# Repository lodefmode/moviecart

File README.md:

# moviecart
Software and Hardware to create full length color movie + audio cartridges for stock Atari 2600

[How to watch different files:](docs/How_To_Update_Content.txt)

[How to encode your own:](https://www.youtube.com/watch?v=WSy6kNrYDSo&list=PLHJZWs7or3edcvVHDeNzGSZABx2JN1WZH)

Pre-Order Kits at:

https://www.tindie.com/products/lodefmode/moviecart-atari-2600/

September 11 1977
-

Introducing MovieCart.

This revolutionary new product will allow for the first time ever, anyone to experience the joy of the silver screen directly from the comfort of their own home, in stunning digital accuracy.
Boasting an impressive 80 x 192 resolution, 7 bit color and 4 bit monaural audio, begin building your full length feature film library today.*

Technical Specs:

   Two fields are alternated at 60 frames per second.
   Each field consists of a checkerboard pattern of 10 x 262 cells.
   Each cell contains one of 128 colours and is 8 pixels wide by 1 pixel deep.
   This produces an effective resolution of 80 x 262 @ 30 frames per second, with 10 colors per line.
   
   Sound is 4 bit mono produced at 15.720 KHz.

   Joystick controls brightness, volume, and shuttle position.
   Console switches control b/w, ten second rewind and full rewind.

   Each field requires 2.5K of data.
   Each second requires the equivalent of 75.5 Combat cartridges, or over half a million cartridges to produce a full length 2 hour movie.

Thanks,

lodef.mode@gmail.com

*Copyright Disclaimer under Section 107 of the copyright act 1976, allowance is made for fair use for purposes such as criticism, comment, news reporting, scholarship, and research. Fair use is a use permitted by copyright statute that might otherwise be infringing. Non-profit, educational or personal use tips the balance in favour of fair use."

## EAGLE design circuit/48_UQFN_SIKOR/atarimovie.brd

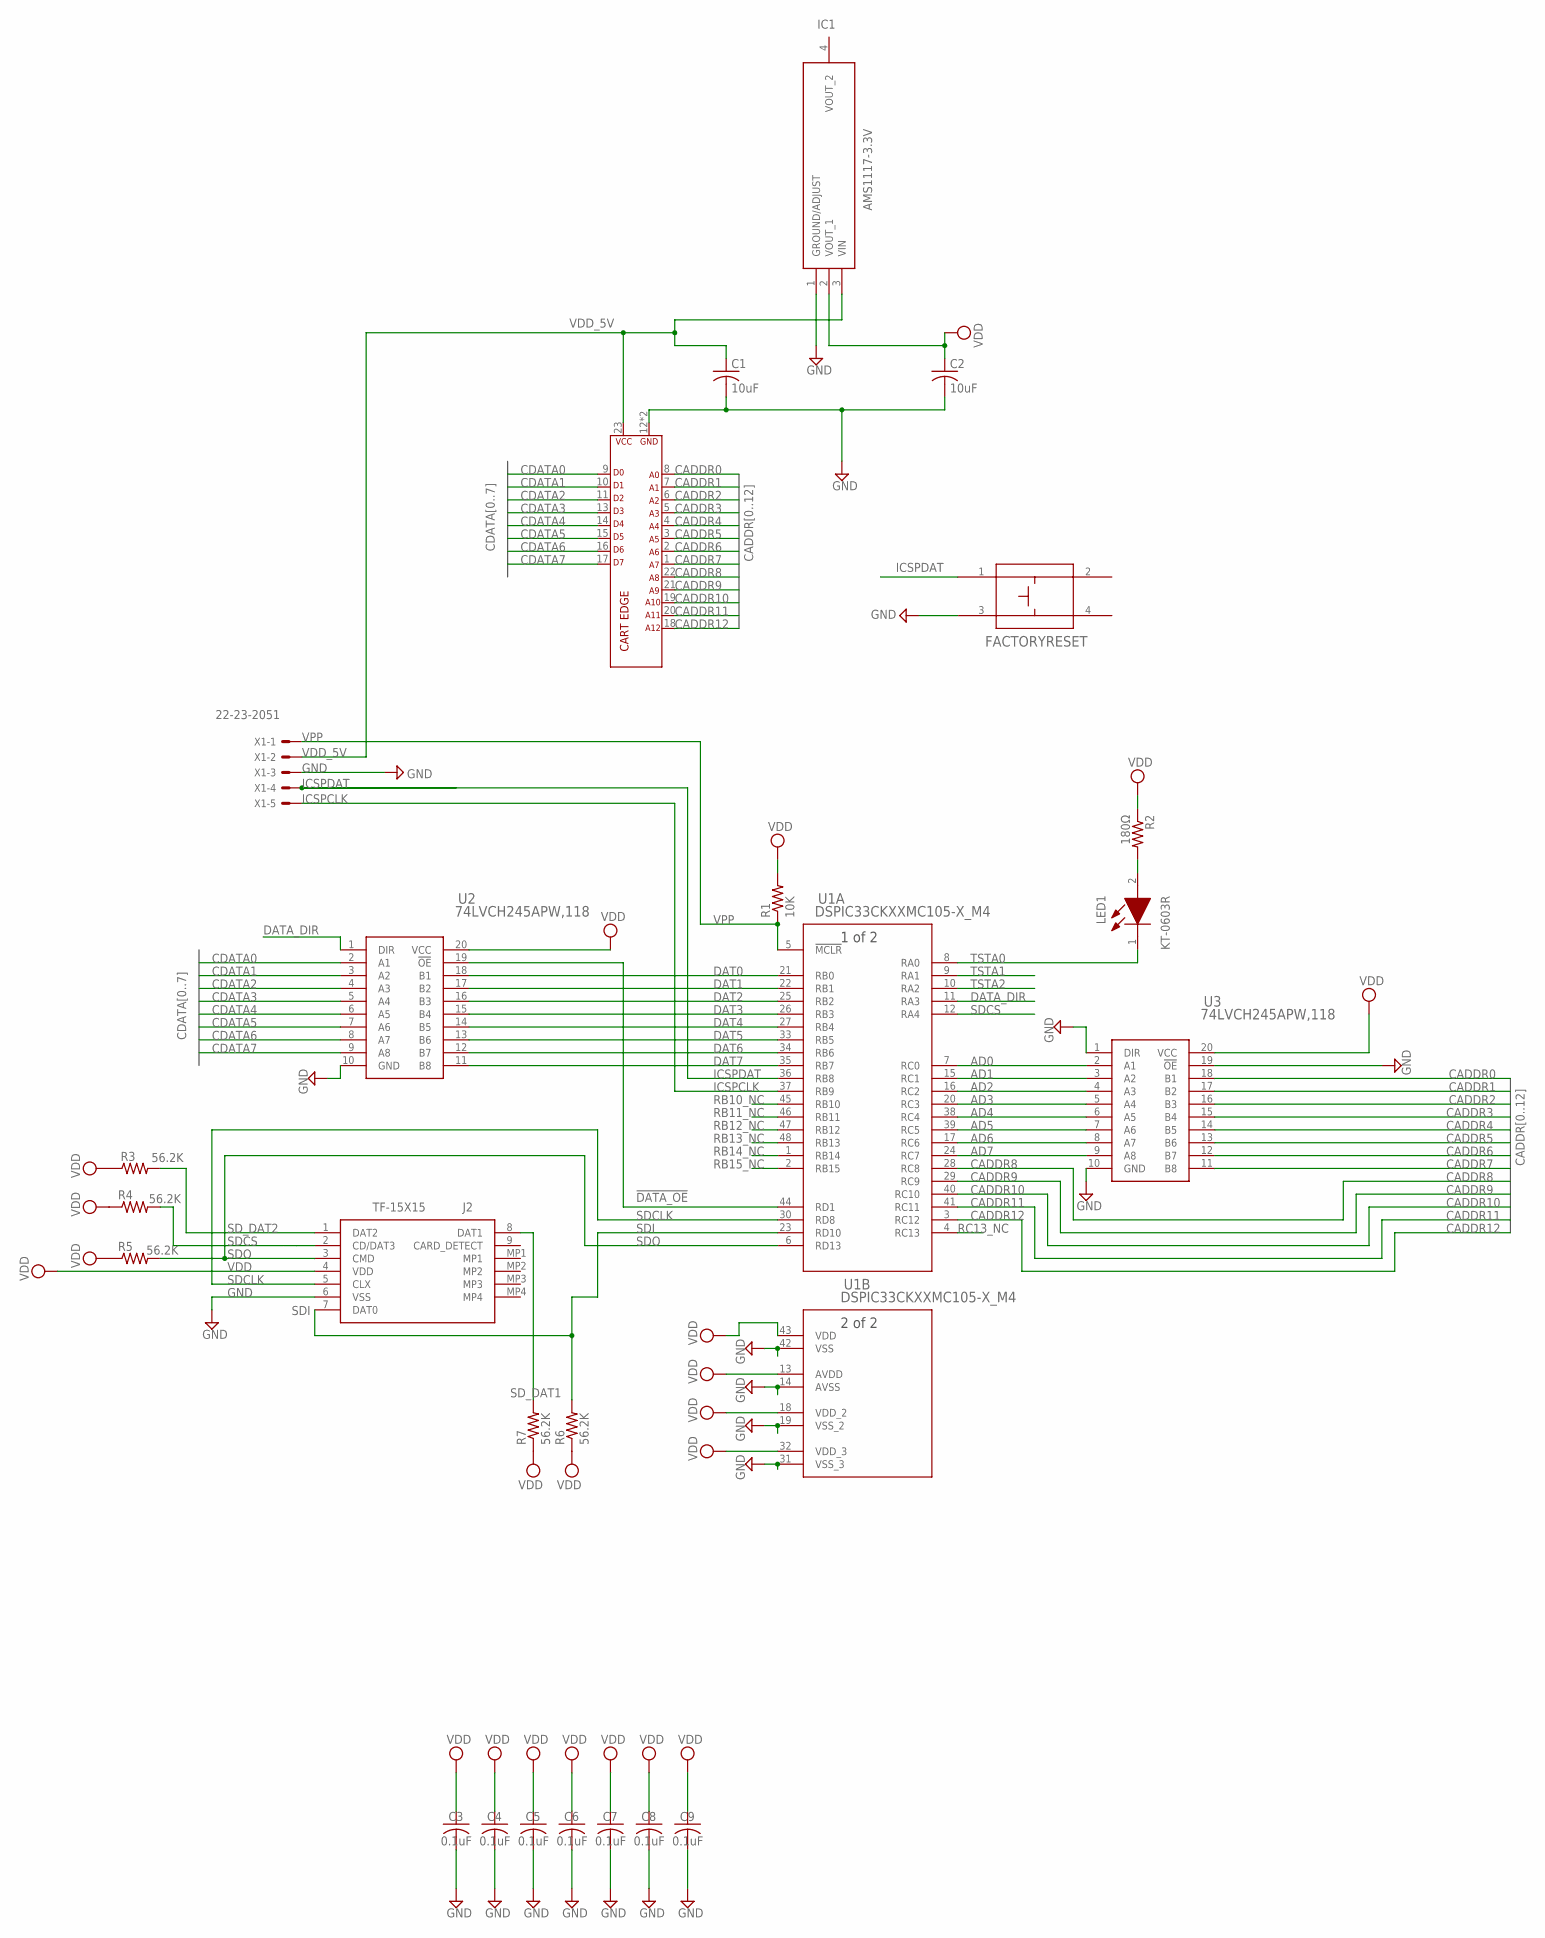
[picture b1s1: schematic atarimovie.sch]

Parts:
C1, C2: 10uF; C0603K
C3, C4, C5, C6, C7, C8, C9: 0.1uF; C0603K
FACTORYRESET: RT3301AF260Q; RT3301_EWI
IC1: AMS1117-3.3V; SOT229P700X180-4N
J1: CARTRIDGE EDGE; MED_TABS_SDACCESS
J2: TF-15X15; TF15X15
LED1: KT-0603R; LEDC1608X70N
R1: 10K; R0603
R2: 180Ω; R0603
R3, R4, R5, R6, R7: 56.2K; R0603
U1: DSPIC33CKXXMC105-X_M4; UQFN48_6X6MC_MCH
U2, U3: 74LVCH245APW,118; SOP65P640X110-20N
X1: 22-23-2051

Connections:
!DATA_OE!: U1.44 (RD1), U2.19 (!OE)
AD0: U1.7 (RC0), U3.2 (A1)
AD1: U1.15 (RC1), U3.3 (A2)
AD2: U1.16 (RC2), U3.4 (A3)
AD3: U1.20 (RC3), U3.5 (A4)
AD4: U1.38 (RC4), U3.6 (A5)
AD5: U1.39 (RC5), U3.7 (A6)
AD6: U1.17 (RC6), U3.8 (A7)
AD7: U1.24 (RC7), U3.9 (A8)
CADDR0: J1.8 (A0), U3.18 (B1)
CADDR1: J1.7 (A1), U3.17 (B2)
CADDR2: J1.6 (A2), U3.16 (B3)
CADDR3: J1.5 (A3), U3.15 (B4)
CADDR4: J1.4 (A4), U3.14 (B5)
CADDR5: J1.3 (A5), U3.13 (B6)
CADDR6: J1.2 (A6), U3.12 (B7)
CADDR7: J1.1 (A7), U3.11 (B8)
CADDR8: J1.22 (A8), U1.28 (RC8)
CADDR9: J1.21 (A9), U1.29 (RC9)
CADDR10: J1.19 (A10), U1.40 (RC10)
CADDR11: J1.20 (A11), U1.41 (RC11)
CADDR12: J1.18 (A12), U1.3 (RC12)
CDATA0: J1.9 (D0), U2.2 (A1)
CDATA1: J1.10 (D1), U2.3 (A2)
CDATA2: J1.11 (D2), U2.4 (A3)
CDATA3: J1.13 (D3), U2.5 (A4)
CDATA4: J1.14 (D4), U2.6 (A5)
CDATA5: J1.15 (D5), U2.7 (A6)
CDATA6: J1.16 (D6), U2.8 (A7)
CDATA7: J1.17 (D7), U2.9 (A8)
DAT0: U1.21 (RB0), U2.18 (B1)
DAT1: U1.22 (RB1), U2.17 (B2)
DAT2: U1.25 (RB2), U2.16 (B3)
DAT3: U1.26 (RB3), U2.15 (B4)
DAT4: U1.27 (RB4), U2.14 (B5)
DAT5: U1.33 (RB5), U2.13 (B6)
DAT6: U1.34 (RB6), U2.12 (B7)
DAT7: U1.35 (RB7), U2.11 (B8)
DATA_DIR: U1.11 (RA3), U2.1 (DIR)
GND: C1.2, C2.2, C3.2, C4.2, C5.2, C6.2, C7.2, C8.2, C9.2, FACTORYRESET.3, IC1.1 (GROUND/ADJUST), J1.12 (GND), J1.24 (GND), J2.6 (VSS), U1.14 (AVSS), U1.19 (VSS_2), U1.31 (VSS_3), U1.42 (VSS), U2.10 (GND), U3.1 (DIR), U3.10 (GND), U3.19 (!OE), X1.3
ICSPCLK: U1.37 (RB9), X1.5
ICSPDAT: FACTORYRESET.1, U1.36 (RB8), X1.4
unnamed: LED1.2 (A), R2.2
RB10_NC: U1.45 (RB10)
RB11_NC: U1.46 (RB11)
RB12_NC: U1.47 (RB12)
RB13_NC: U1.48 (RB13)
RB14_NC: U1.1 (RB14)
RB15_NC: U1.2 (RB15)
RC13_NC: U1.4 (RC13)
SDCLK: J2.5 (CLX), U1.30 (RD8)
SDCS: J2.2 (CD/DAT3), R4.2, U1.12 (RA4)
SDI: J2.7 (DAT0), R6.2, U1.23 (RD10)
SDO: J2.3 (CMD), R5.2, U1.6 (RD13)
SD_DAT1: J2.8 (DAT1), R7.2
SD_DAT2: J2.1 (DAT2), R3.2
TSTA0: LED1.1 (K), U1.8 (RA0)
TSTA1: U1.9 (RA1)
TSTA2: U1.10 (RA2)
VDD: C2.1, C3.1, C4.1, C5.1, C6.1, C7.1, C8.1, C9.1, IC1.2 (VOUT_1), J2.4 (VDD), R1.2, R2.1, R3.1, R4.1, R5.1, R6.1, R7.1, U1.13 (AVDD), U1.18 (VDD_2), U1.32 (VDD_3), U1.43 (VDD), U2.20 (VCC), U3.20 (VCC)
VDD_5V: C1.1, IC1.3 (VIN), J1.23 (VCC), X1.2
VPP: R1.1, U1.5 (!MCLR), X1.1

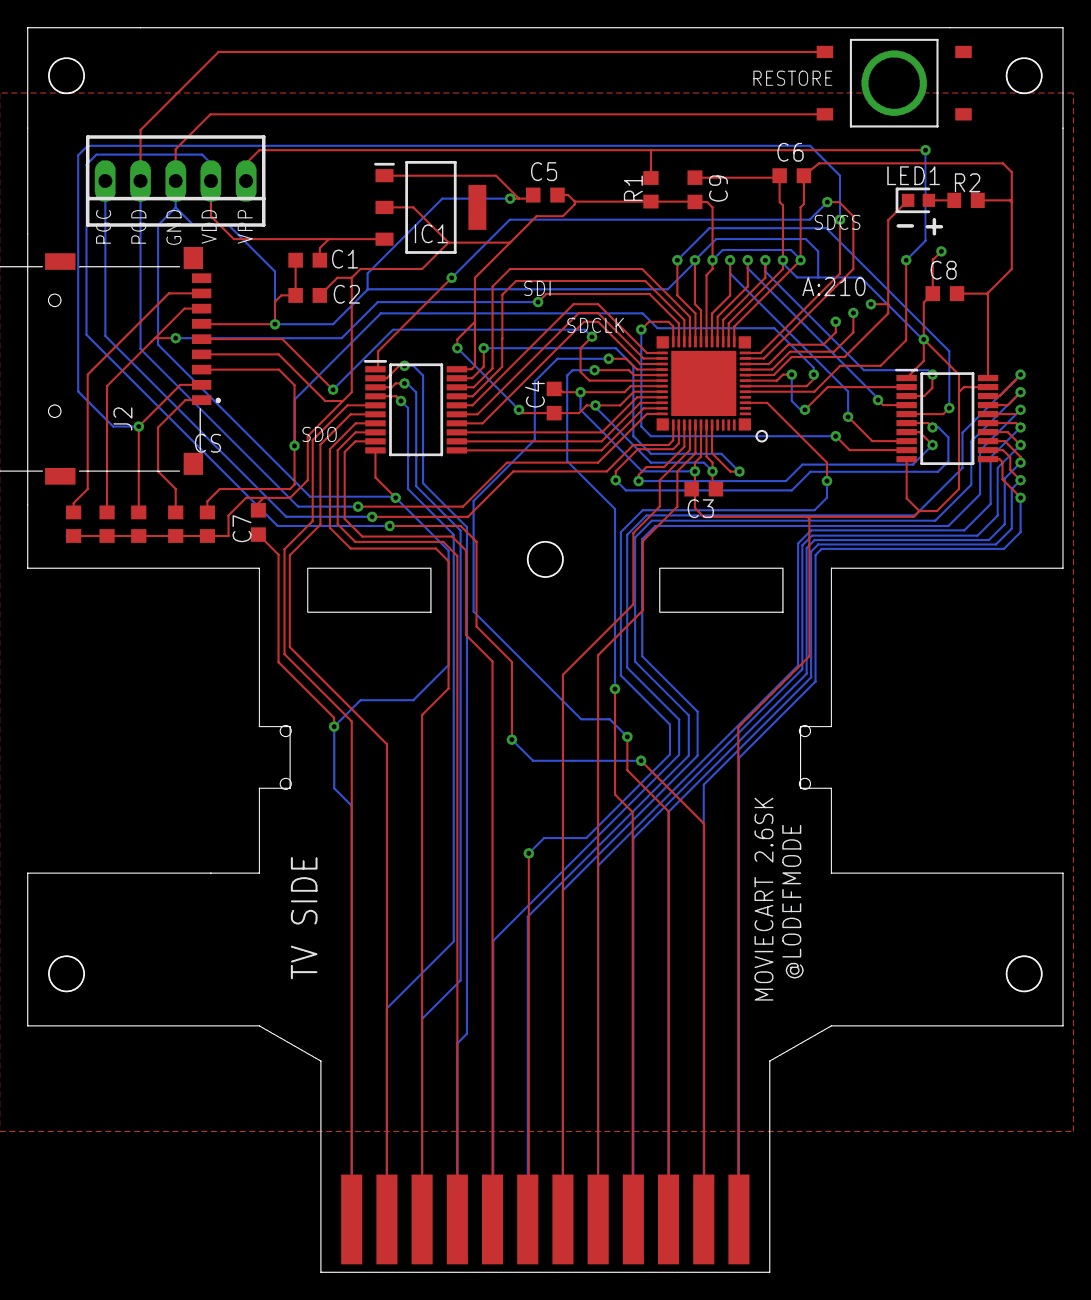
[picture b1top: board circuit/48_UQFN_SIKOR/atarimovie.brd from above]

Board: 2 copper layers, 74.7 x 89.8 mm, 25 parts (1 on the bottom side), 53 nets.

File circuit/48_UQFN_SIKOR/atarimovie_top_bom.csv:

Comment,Designator,Footprint,LCSC Part #
0.1uF,C3 C4 C5 C6 C7 C8 C9,C0603K,
10K,R1,R0603,
10uF,C1 C2,C0603K,
56.2K,R3 R4 R5 R6 R7,R0603,
74LVCH245APW 118,U2,SOP65P640X110-20N,
74LVCH245APW 118,U3,SOP65P640X110-20N,
180Ω,R2,R0603,
AMS1117-3.3V,IC1,SOT229P700X180-4N,
CARTRIDGE EDGE,J1,MED_TABS_SDACCESS,
DSPIC33CKXXMC105-X_M4,U1,UQFN48_6X6MC_MCH,
KT-0603R,LED1,LEDC1608X70N,
RT3301AF260Q,FACTORYRESET,RT3301_EWI,
TF-15X15,J2,TF15X15,

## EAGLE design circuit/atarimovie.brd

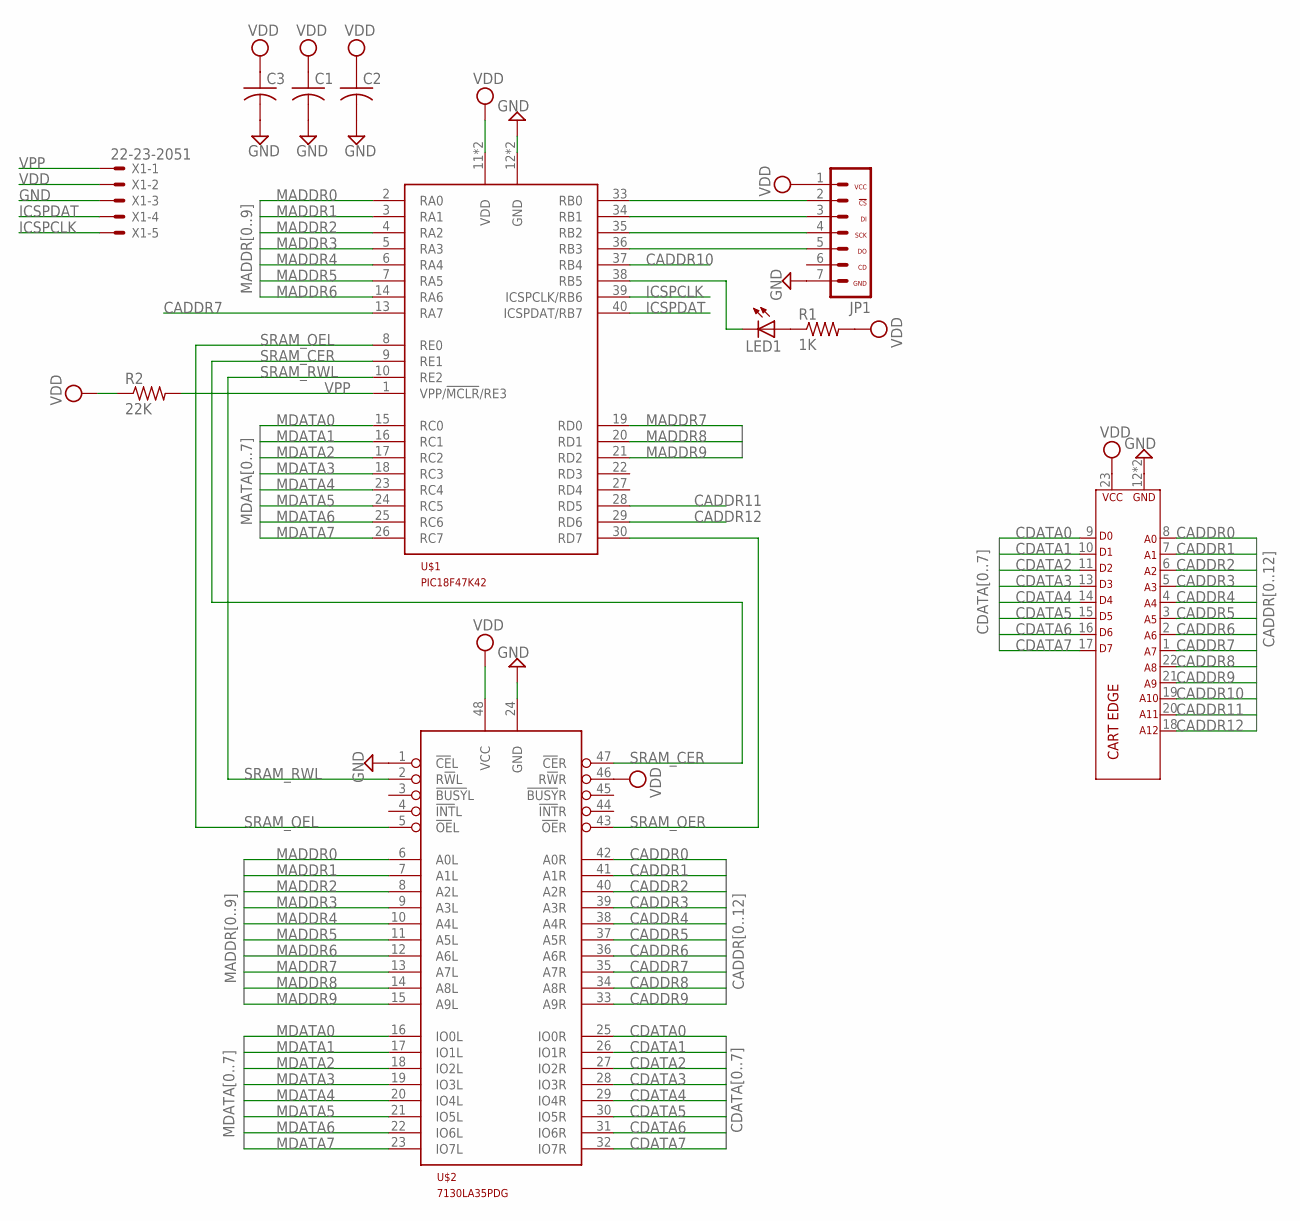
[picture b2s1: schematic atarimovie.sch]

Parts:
C1, C2, C3: C-US050-025X075; C050-025X075
J1: ATARI-2600MED_NOHOLE; MED_NOHOLE
JP1: USD_SHIFTER
LED1: LED3MM
R1: 1K; 0204/7
R2: 22K; 0204/7
U$1: PIC18F47K42; DIP40
U$2: 7130LA35PDG; DIP48
X1: 22-23-2051

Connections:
CADDR0: J1.8 (A0), U$2.42 (A0R)
CADDR1: J1.7 (A1), U$2.41 (A1R)
CADDR2: J1.6 (A2), U$2.40 (A2R)
CADDR3: J1.5 (A3), U$2.39 (A3R)
CADDR4: J1.4 (A4), U$2.38 (A4R)
CADDR5: J1.3 (A5), U$2.37 (A5R)
CADDR6: J1.2 (A6), U$2.36 (A6R)
CADDR7: J1.1 (A7), U$1.13 (RA7), U$2.35 (A7R)
CADDR8: J1.22 (A8), U$2.34 (A8R)
CADDR9: J1.21 (A9), U$2.33 (A9R)
CADDR10: J1.19 (A10), U$1.37 (RB4)
CADDR11: J1.20 (A11), U$1.28 (RD5)
CADDR12: J1.18 (A12), U$1.29 (RD6)
CDATA0: J1.9 (D0), U$2.25 (IO0R)
CDATA1: J1.10 (D1), U$2.26 (IO1R)
CDATA2: J1.11 (D2), U$2.27 (IO2R)
CDATA3: J1.13 (D3), U$2.28 (IO3R)
CDATA4: J1.14 (D4), U$2.29 (IO4R)
CDATA5: J1.15 (D5), U$2.30 (IO5R)
CDATA6: J1.16 (D6), U$2.31 (IO6R)
CDATA7: J1.17 (D7), U$2.32 (IO7R)
GND: C1.2, C2.2, C3.2, J1.12 (GND), J1.24 (GND), JP1.7 (GND), U$1.12 (GND), U$1.31 (GND), U$2.1 (!CE!L), U$2.24 (GND), X1.3
ICSPCLK: U$1.39 (ICSPCLK/RB6), X1.5
ICSPDAT: U$1.40 (ICSPDAT/RB7), X1.4
MADDR0: U$1.2 (RA0), U$2.6 (A0L)
MADDR1: U$1.3 (RA1), U$2.7 (A1L)
MADDR2: U$1.4 (RA2), U$2.8 (A2L)
MADDR3: U$1.5 (RA3), U$2.9 (A3L)
MADDR4: U$1.6 (RA4), U$2.10 (A4L)
MADDR5: U$1.7 (RA5), U$2.11 (A5L)
MADDR6: U$1.14 (RA6), U$2.12 (A6L)
MADDR7: U$1.19 (RD0), U$2.13 (A7L)
MADDR8: U$1.20 (RD1), U$2.14 (A8L)
MADDR9: U$1.21 (RD2), U$2.15 (A9L)
MDATA0: U$1.15 (RC0), U$2.16 (IO0L)
MDATA1: U$1.16 (RC1), U$2.17 (IO1L)
MDATA2: U$1.17 (RC2), U$2.18 (IO2L)
MDATA3: U$1.18 (RC3), U$2.19 (IO3L)
MDATA4: U$1.23 (RC4), U$2.20 (IO4L)
MDATA5: U$1.24 (RC5), U$2.21 (IO5L)
MDATA6: U$1.25 (RC6), U$2.22 (IO6L)
MDATA7: U$1.26 (RC7), U$2.23 (IO7L)
unnamed: JP1.2 (!CS), U$1.33 (RB0)
unnamed: JP1.3 (DI), U$1.34 (RB1)
unnamed: JP1.4 (SCK), U$1.35 (RB2)
unnamed: JP1.5 (DO), U$1.36 (RB3)
unnamed: LED1.A, R1.1
unnamed: LED1.K (C), U$1.38 (RB5)
SRAM_CER: U$1.9 (RE1), U$2.47 (!CE!R)
SRAM_OEL: U$1.8 (RE0), U$2.5 (!OE!L)
SRAM_OER: U$1.30 (RD7), U$2.43 (!OE!R)
SRAM_RWL: U$1.10 (RE2), U$2.2 (R!W!L)
VDD: C1.1, C2.1, C3.1, J1.23 (VCC), JP1.1 (VCC), R1.2, R2.1, U$1.11 (VDD), U$1.32 (VDD), U$2.46 (R!W!R), U$2.48 (VCC), X1.2
VPP: R2.2, U$1.1 (VPP/!MCLR!/RE3), X1.1

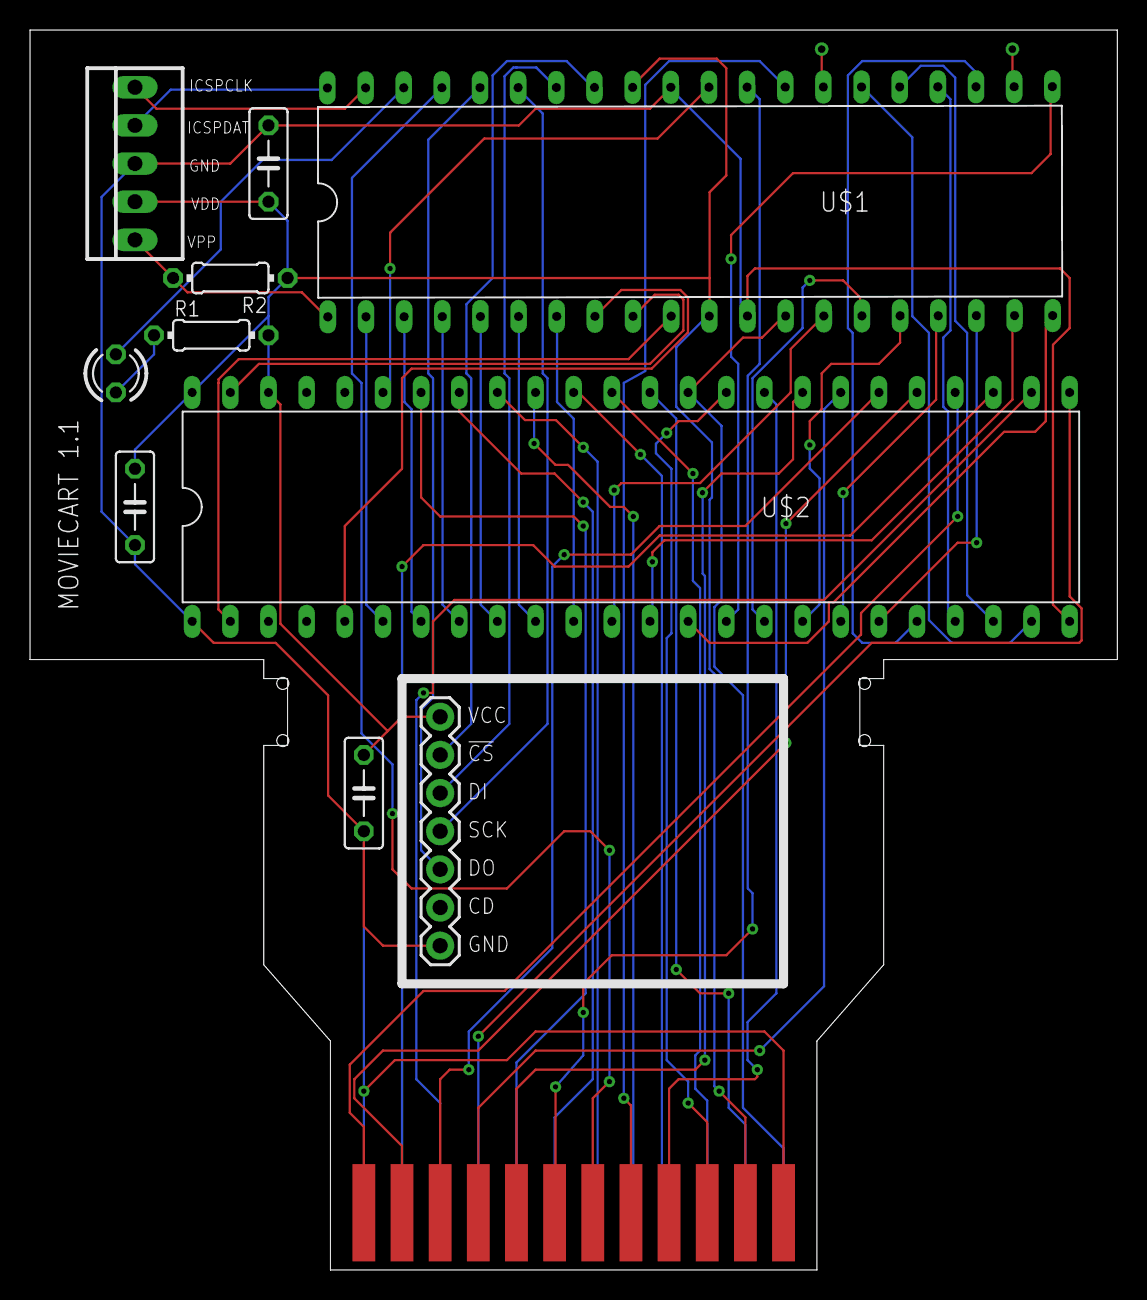
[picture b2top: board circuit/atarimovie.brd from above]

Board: 2 copper layers, 72.4 x 82.5 mm, 11 parts (1 on the bottom side), 54 nets.

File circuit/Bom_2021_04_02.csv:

"Index","Quantity","Part Number","Manufacturer Part Number","Description","Customer Reference","Available","Backorder","Unit Price","Extended Price CAD"
"1","1","1568-1356-ND","DEV-13743","SPARKFUN LEVEL SHIFTING MICROSD","","1","0","7.47000","7.47"
"2","1","160-1140-ND","LTL-4222N","LED RED CLEAR T-1 T/H","","1","0","0.49000","0.49"
"3","3","478-3188-ND","SR215C104KAR","CAP CER 0.1UF 50V X7R RADIAL","","3","0","0.69000","2.07"
"4","1","800-2448-5-ND","7130LA35PDG","IC SRAM 8KBIT PARALLEL 48DIP","","1","0","17.63000","17.63"
"5","1","CF18JT22K0CT-ND","CF18JT22K0","RES 22K OHM 1/8W 5% CF AXIAL","","1","0","0.14000","0.14"
"6","1","PIC18F47K42-I/P-ND","PIC18F47K42-I/P","IC MCU 8BIT 128KB FLASH 40DIP","","1","0","4.35000","4.35"
"7","1","S7038-ND","PPPC051LFBN-RC","CONN HDR 5POS 0.1 GOLD PCB","","1","0","0.67000","0.67"
"8","1","CF18JT1K00CT-ND","CF18JT1K00","RES 1K OHM 1/8W 5% CF AXIAL","","1","0","0.14000","0.14"
"9","1","SAM1027-05-ND","TSW-105-06-T-S","CONN HEADER VERT 5POS 2.54MM","","1","0","0.56000","0.56"

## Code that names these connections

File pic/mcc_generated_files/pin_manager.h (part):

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// get/set IO_RA0 aliases
#define IO_RA0_TRIS                 TRISAbits.TRISA0
#define IO_RA0_LAT                  LATAbits.LATA0
#define IO_RA0_PORT                 PORTAbits.RA0
#define IO_RA0_WPU                  WPUAbits.WPUA0
#define IO_RA0_OD                   ODCONAbits.ODCA0
#define IO_RA0_ANS                  ANSELAbits.ANSELA0
#define IO_RA0_SetHigh()            do { LATAbits.LATA0 = 1; } while(0)
#define IO_RA0_SetLow()             do { LATAbits.LATA0 = 0; } while(0)
#define IO_RA0_Toggle()             do { LATAbits.LATA0 = ~LATAbits.LATA0; } while(0)
#define IO_RA0_GetValue()           PORTAbits.RA0
#define IO_RA0_SetDigitalInput()    do { TRISAbits.TRISA0 = 1; } while(0)
#define IO_RA0_SetDigitalOutput()   do { TRISAbits.TRISA0 = 0; } while(0)
#define IO_RA0_SetPullup()          do { WPUAbits.WPUA0 = 1; } while(0)
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// get/set IO_RA1 aliases
#define IO_RA1_TRIS                 TRISAbits.TRISA1
#define IO_RA1_LAT                  LATAbits.LATA1
#define IO_RA1_PORT                 PORTAbits.RA1
#define IO_RA1_WPU                  WPUAbits.WPUA1
#define IO_RA1_OD                   ODCONAbits.ODCA1
#define IO_RA1_ANS                  ANSELAbits.ANSELA1
#define IO_RA1_SetHigh()            do { LATAbits.LATA1 = 1; } while(0)
#define IO_RA1_SetLow()             do { LATAbits.LATA1 = 0; } while(0)
#define IO_RA1_Toggle()             do { LATAbits.LATA1 = ~LATAbits.LATA1; } while(0)
#define IO_RA1_GetValue()           PORTAbits.RA1
#define IO_RA1_SetDigitalInput()    do { TRISAbits.TRISA1 = 1; } while(0)
#define IO_RA1_SetDigitalOutput()   do { TRISAbits.TRISA1 = 0; } while(0)
#define IO_RA1_SetPullup()          do { WPUAbits.WPUA1 = 1; } while(0)
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// get/set IO_RA2 aliases
#define IO_RA2_TRIS                 TRISAbits.TRISA2
#define IO_RA2_LAT                  LATAbits.LATA2
#define IO_RA2_PORT                 PORTAbits.RA2
#define IO_RA2_WPU                  WPUAbits.WPUA2
#define IO_RA2_OD                   ODCONAbits.ODCA2
#define IO_RA2_ANS                  ANSELAbits.ANSELA2
#define IO_RA2_SetHigh()            do { LATAbits.LATA2 = 1; } while(0)
#define IO_RA2_SetLow()             do { LATAbits.LATA2 = 0; } while(0)
#define IO_RA2_Toggle()             do { LATAbits.LATA2 = ~LATAbits.LATA2; } while(0)
#define IO_RA2_GetValue()           PORTAbits.RA2
#define IO_RA2_SetDigitalInput()    do { TRISAbits.TRISA2 = 1; } while(0)
#define IO_RA2_SetDigitalOutput()   do { TRISAbits.TRISA2 = 0; } while(0)
#define IO_RA2_SetPullup()          do { WPUAbits.WPUA2 = 1; } while(0)
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// get/set IO_RA3 aliases
#define IO_RA3_TRIS                 TRISAbits.TRISA3
#define IO_RA3_LAT                  LATAbits.LATA3
#define IO_RA3_PORT                 PORTAbits.RA3
#define IO_RA3_WPU                  WPUAbits.WPUA3
#define IO_RA3_OD                   ODCONAbits.ODCA3
#define IO_RA3_ANS                  ANSELAbits.ANSELA3
#define IO_RA3_SetHigh()            do { LATAbits.LATA3 = 1; } while(0)
#define IO_RA3_SetLow()             do { LATAbits.LATA3 = 0; } while(0)
#define IO_RA3_Toggle()             do { LATAbits.LATA3 = ~LATAbits.LATA3; } while(0)
#define IO_RA3_GetValue()           PORTAbits.RA3
#define IO_RA3_SetDigitalInput()    do { TRISAbits.TRISA3 = 1; } while(0)
#define IO_RA3_SetDigitalOutput()   do { TRISAbits.TRISA3 = 0; } while(0)
#define IO_RA3_SetPullup()          do { WPUAbits.WPUA3 = 1; } while(0)
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// get/set IO_RA4 aliases
#define IO_RA4_TRIS                 TRISAbits.TRISA4
#define IO_RA4_LAT                  LATAbits.LATA4
#define IO_RA4_PORT                 PORTAbits.RA4
#define IO_RA4_WPU                  WPUAbits.WPUA4
#define IO_RA4_OD                   ODCONAbits.ODCA4
#define IO_RA4_ANS                  ANSELAbits.ANSELA4
#define IO_RA4_SetHigh()            do { LATAbits.LATA4 = 1; } while(0)
#define IO_RA4_SetLow()             do { LATAbits.LATA4 = 0; } while(0)
#define IO_RA4_Toggle()             do { LATAbits.LATA4 = ~LATAbits.LATA4; } while(0)
#define IO_RA4_GetValue()           PORTAbits.RA4
#define IO_RA4_SetDigitalInput()    do { TRISAbits.TRISA4 = 1; } while(0)
#define IO_RA4_SetDigitalOutput()   do { TRISAbits.TRISA4 = 0; } while(0)
#define IO_RA4_SetPullup()          do { WPUAbits.WPUA4 = 1; } while(0)
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// get/set IO_RA5 aliases
#define IO_RA5_TRIS                 TRISAbits.TRISA5
#define IO_RA5_LAT                  LATAbits.LATA5
#define IO_RA5_PORT                 PORTAbits.RA5
#define IO_RA5_WPU                  WPUAbits.WPUA5
#define IO_RA5_OD                   ODCONAbits.ODCA5
#define IO_RA5_ANS                  ANSELAbits.ANSELA5
#define IO_RA5_SetHigh()            do { LATAbits.LATA5 = 1; } while(0)
#define IO_RA5_SetLow()             do { LATAbits.LATA5 = 0; } while(0)
#define IO_RA5_Toggle()             do { LATAbits.LATA5 = ~LATAbits.LATA5; } while(0)
#define IO_RA5_GetValue()           PORTAbits.RA5
#define IO_RA5_SetDigitalInput()    do { TRISAbits.TRISA5 = 1; } while(0)
#define IO_RA5_SetDigitalOutput()   do { TRISAbits.TRISA5 = 0; } while(0)
#define IO_RA5_SetPullup()          do { WPUAbits.WPUA5 = 1; } while(0)
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// get/set IO_RA6 aliases
#define IO_RA6_TRIS                 TRISAbits.TRISA6
#define IO_RA6_LAT                  LATAbits.LATA6
#define IO_RA6_PORT                 PORTAbits.RA6
#define IO_RA6_WPU                  WPUAbits.WPUA6
#define IO_RA6_OD                   ODCONAbits.ODCA6
#define IO_RA6_ANS                  ANSELAbits.ANSELA6
#define IO_RA6_SetHigh()            do { LATAbits.LATA6 = 1; } while(0)
#define IO_RA6_SetLow()             do { LATAbits.LATA6 = 0; } while(0)
#define IO_RA6_Toggle()             do { LATAbits.LATA6 = ~LATAbits.LATA6; } while(0)
#define IO_RA6_GetValue()           PORTAbits.RA6
#define IO_RA6_SetDigitalInput()    do { TRISAbits.TRISA6 = 1; } while(0)
#define IO_RA6_SetDigitalOutput()   do { TRISAbits.TRISA6 = 0; } while(0)
#define IO_RA6_SetPullup()          do { WPUAbits.WPUA6 = 1; } while(0)
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#define RB1_SetHigh()               do { LATBbits.LATB1 = 1; } while(0)
#define RB1_SetLow()                do { LATBbits.LATB1 = 0; } while(0)
#define RB1_Toggle()                do { LATBbits.LATB1 = ~LATBbits.LATB1; } while(0)
#define RB1_GetValue()              PORTBbits.RB1
#define RB1_SetDigitalInput()       do { TRISBbits.TRISB1 = 1; } while(0)
#define RB1_SetDigitalOutput()      do { TRISBbits.TRISB1 = 0; } while(0)
#define RB1_SetPullup()             do { WPUBbits.WPUB1 = 1; } while(0)
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#define RB2_SetHigh()               do { LATBbits.LATB2 = 1; } while(0)
#define RB2_SetLow()                do { LATBbits.LATB2 = 0; } while(0)
#define RB2_Toggle()                do { LATBbits.LATB2 = ~LATBbits.LATB2; } while(0)
#define RB2_GetValue()              PORTBbits.RB2
#define RB2_SetDigitalInput()       do { TRISBbits.TRISB2 = 1; } while(0)
#define RB2_SetDigitalOutput()      do { TRISBbits.TRISB2 = 0; } while(0)
#define RB2_SetPullup()             do { WPUBbits.WPUB2 = 1; } while(0)
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#define RB3_SetHigh()               do { LATBbits.LATB3 = 1; } while(0)
#define RB3_SetLow()                do { LATBbits.LATB3 = 0; } while(0)
#define RB3_Toggle()                do { LATBbits.LATB3 = ~LATBbits.LATB3; } while(0)
#define RB3_GetValue()              PORTBbits.RB3
#define RB3_SetDigitalInput()       do { TRISBbits.TRISB3 = 1; } while(0)
#define RB3_SetDigitalOutput()      do { TRISBbits.TRISB3 = 0; } while(0)
#define RB3_SetPullup()             do { WPUBbits.WPUB3 = 1; } while(0)
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// get/set IO_RB4 aliases
#define IO_RB4_TRIS                 TRISBbits.TRISB4
#define IO_RB4_LAT                  LATBbits.LATB4
#define IO_RB4_PORT                 PORTBbits.RB4
#define IO_RB4_WPU                  WPUBbits.WPUB4
#define IO_RB4_OD                   ODCONBbits.ODCB4
#define IO_RB4_ANS                  ANSELBbits.ANSELB4
#define IO_RB4_SetHigh()            do { LATBbits.LATB4 = 1; } while(0)
#define IO_RB4_SetLow()             do { LATBbits.LATB4 = 0; } while(0)
#define IO_RB4_Toggle()             do { LATBbits.LATB4 = ~LATBbits.LATB4; } while(0)
#define IO_RB4_GetValue()           PORTBbits.RB4
#define IO_RB4_SetDigitalInput()    do { TRISBbits.TRISB4 = 1; } while(0)
#define IO_RB4_SetDigitalOutput()   do { TRISBbits.TRISB4 = 0; } while(0)
#define IO_RB4_SetPullup()          do { WPUBbits.WPUB4 = 1; } while(0)
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// get/set IO_RB5 aliases
#define IO_RB5_TRIS                 TRISBbits.TRISB5
#define IO_RB5_LAT                  LATBbits.LATB5
#define IO_RB5_PORT                 PORTBbits.RB5
#define IO_RB5_WPU                  WPUBbits.WPUB5
#define IO_RB5_OD                   ODCONBbits.ODCB5
#define IO_RB5_ANS                  ANSELBbits.ANSELB5
#define IO_RB5_SetHigh()            do { LATBbits.LATB5 = 1; } while(0)
#define IO_RB5_SetLow()             do { LATBbits.LATB5 = 0; } while(0)
#define IO_RB5_Toggle()             do { LATBbits.LATB5 = ~LATBbits.LATB5; } while(0)
#define IO_RB5_GetValue()           PORTBbits.RB5
#define IO_RB5_SetDigitalInput()    do { TRISBbits.TRISB5 = 1; } while(0)
#define IO_RB5_SetDigitalOutput()   do { TRISBbits.TRISB5 = 0; } while(0)
#define IO_RB5_SetPullup()          do { WPUBbits.WPUB5 = 1; } while(0)
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
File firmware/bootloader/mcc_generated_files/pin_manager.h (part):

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*/
/**
  @Summary
    Sets the GPIO pin, RA0, high using LATA0.

  @Description
    Sets the GPIO pin, RA0, high using LATA0.

  @Preconditions
    The RA0 must be set to an output.
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#define IO_RA0_SetHigh()          (_LATA0 = 1)
/**
  @Summary
    Sets the GPIO pin, RA0, low using LATA0.

  @Description
    Sets the GPIO pin, RA0, low using LATA0.

  @Preconditions
    The RA0 must be set to an output.
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#define IO_RA0_SetLow()           (_LATA0 = 0)
/**
  @Summary
    Toggles the GPIO pin, RA0, using LATA0.

  @Description
    Toggles the GPIO pin, RA0, using LATA0.

  @Preconditions
    The RA0 must be set to an output.
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#define IO_RA0_Toggle()           (_LATA0 ^= 1)
/**
  @Summary
    Reads the value of the GPIO pin, RA0.

  @Description
    Reads the value of the GPIO pin, RA0.

  @Preconditions
    None.
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    </code>

*/
#define IO_RA0_GetValue()         _RA0
/**
  @Summary
    Configures the GPIO pin, RA0, as an input.

  @Description
    Configures the GPIO pin, RA0, as an input.

  @Preconditions
    None.
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#define IO_RA0_SetDigitalInput()  (_TRISA0 = 1)
/**
  @Summary
    Configures the GPIO pin, RA0, as an output.

  @Description
    Configures the GPIO pin, RA0, as an output.

  @Preconditions
    None.
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#define IO_RA0_SetDigitalOutput() (_TRISA0 = 0)
/**
  @Summary
    Sets the GPIO pin, RA1, high using LATA1.

  @Description
    Sets the GPIO pin, RA1, high using LATA1.

  @Preconditions
    The RA1 must be set to an output.
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#define IO_RA1_SetHigh()          (_LATA1 = 1)
/**
  @Summary
    Sets the GPIO pin, RA1, low using LATA1.

  @Description
    Sets the GPIO pin, RA1, low using LATA1.

  @Preconditions
    The RA1 must be set to an output.
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#define IO_RA1_SetLow()           (_LATA1 = 0)
/**
  @Summary
    Toggles the GPIO pin, RA1, using LATA1.

  @Description
    Toggles the GPIO pin, RA1, using LATA1.

  @Preconditions
    The RA1 must be set to an output.
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#define IO_RA1_Toggle()           (_LATA1 ^= 1)
/**
  @Summary
    Reads the value of the GPIO pin, RA1.

  @Description
    Reads the value of the GPIO pin, RA1.

  @Preconditions
    None.
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    </code>

*/
#define IO_RA1_GetValue()         _RA1
/**
  @Summary
    Configures the GPIO pin, RA1, as an input.

  @Description
    Configures the GPIO pin, RA1, as an input.

  @Preconditions
    None.
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#define IO_RA1_SetDigitalInput()  (_TRISA1 = 1)
/**
  @Summary
    Configures the GPIO pin, RA1, as an output.

  @Description
    Configures the GPIO pin, RA1, as an output.

  @Preconditions
    None.
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#define IO_RA1_SetDigitalOutput() (_TRISA1 = 0)
/**
  @Summary
    Sets the GPIO pin, RA2, high using LATA2.

  @Description
    Sets the GPIO pin, RA2, high using LATA2.

  @Preconditions
    The RA2 must be set to an output.
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#define IO_RA2_SetHigh()          (_LATA2 = 1)
/**
  @Summary
    Sets the GPIO pin, RA2, low using LATA2.

  @Description
    Sets the GPIO pin, RA2, low using LATA2.

  @Preconditions
    The RA2 must be set to an output.
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#define IO_RA2_SetLow()           (_LATA2 = 0)
/**
  @Summary
    Toggles the GPIO pin, RA2, using LATA2.

  @Description
    Toggles the GPIO pin, RA2, using LATA2.

  @Preconditions
    The RA2 must be set to an output.
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#define IO_RA2_Toggle()           (_LATA2 ^= 1)
/**
  @Summary
    Reads the value of the GPIO pin, RA2.

  @Description
    Reads the value of the GPIO pin, RA2.

  @Preconditions
    None.
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    </code>

*/
#define IO_RA2_GetValue()         _RA2
/**
  @Summary
    Configures the GPIO pin, RA2, as an input.

  @Description
    Configures the GPIO pin, RA2, as an input.

  @Preconditions
    None.
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#define IO_RA2_SetDigitalInput()  (_TRISA2 = 1)
/**
  @Summary
    Configures the GPIO pin, RA2, as an output.

  @Description
    Configures the GPIO pin, RA2, as an output.

  @Preconditions
    None.
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#define IO_RA2_SetDigitalOutput() (_TRISA2 = 0)
/**
  @Summary
    Sets the GPIO pin, RA3, high using LATA3.

  @Description
    Sets the GPIO pin, RA3, high using LATA3.

  @Preconditions
    The RA3 must be set to an output.
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#define IO_RA3_SetHigh()          (_LATA3 = 1)
/**
  @Summary
    Sets the GPIO pin, RA3, low using LATA3.

  @Description
    Sets the GPIO pin, RA3, low using LATA3.

  @Preconditions
    The RA3 must be set to an output.
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#define IO_RA3_SetLow()           (_LATA3 = 0)
/**
  @Summary
    Toggles the GPIO pin, RA3, using LATA3.

  @Description
    Toggles the GPIO pin, RA3, using LATA3.

  @Preconditions
    The RA3 must be set to an output.
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#define IO_RA3_Toggle()           (_LATA3 ^= 1)
/**
  @Summary
    Reads the value of the GPIO pin, RA3.

  @Description
    Reads the value of the GPIO pin, RA3.

  @Preconditions
    None.
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    </code>

*/
#define IO_RA3_GetValue()         _RA3
/**
  @Summary
    Configures the GPIO pin, RA3, as an input.

  @Description
    Configures the GPIO pin, RA3, as an input.

  @Preconditions
    None.
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#define IO_RA3_SetDigitalInput()  (_TRISA3 = 1)
/**
  @Summary
    Configures the GPIO pin, RA3, as an output.

  @Description
    Configures the GPIO pin, RA3, as an output.

  @Preconditions
    None.
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#define IO_RA3_SetDigitalOutput() (_TRISA3 = 0)
/**
  @Summary
    Sets the GPIO pin, RA4, high using LATA4.

  @Description
    Sets the GPIO pin, RA4, high using LATA4.

  @Preconditions
    The RA4 must be set to an output.
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#define IO_RA4_SetHigh()          (_LATA4 = 1)
/**
  @Summary
    Sets the GPIO pin, RA4, low using LATA4.

  @Description
    Sets the GPIO pin, RA4, low using LATA4.

  @Preconditions
    The RA4 must be set to an output.
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#define IO_RA4_SetLow()           (_LATA4 = 0)
/**
  @Summary
    Toggles the GPIO pin, RA4, using LATA4.

  @Description
    Toggles the GPIO pin, RA4, using LATA4.

  @Preconditions
    The RA4 must be set to an output.
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#define IO_RA4_Toggle()           (_LATA4 ^= 1)
/**
  @Summary
    Reads the value of the GPIO pin, RA4.

  @Description
    Reads the value of the GPIO pin, RA4.

  @Preconditions
    None.
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    </code>

*/
#define IO_RA4_GetValue()         _RA4
/**
  @Summary
    Configures the GPIO pin, RA4, as an input.

  @Description
    Configures the GPIO pin, RA4, as an input.

  @Preconditions
    None.
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#define IO_RA4_SetDigitalInput()  (_TRISA4 = 1)
/**
  @Summary
    Configures the GPIO pin, RA4, as an output.

  @Description
    Configures the GPIO pin, RA4, as an output.

  @Preconditions
    None.
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#define IO_RA4_SetDigitalOutput() (_TRISA4 = 0)
/**
  @Summary
    Sets the GPIO pin, RB0, high using LATB0.

  @Description
    Sets the GPIO pin, RB0, high using LATB0.

  @Preconditions
    The RB0 must be set to an output.
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#define IO_RB0_SetHigh()          (_LATB0 = 1)
/**
  @Summary
    Sets the GPIO pin, RB0, low using LATB0.

  @Description
    Sets the GPIO pin, RB0, low using LATB0.

  @Preconditions
    The RB0 must be set to an output.
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#define IO_RB0_SetLow()           (_LATB0 = 0)
/**
  @Summary
    Toggles the GPIO pin, RB0, using LATB0.

  @Description
    Toggles the GPIO pin, RB0, using LATB0.

  @Preconditions
    The RB0 must be set to an output.
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#define IO_RB0_Toggle()           (_LATB0 ^= 1)
/**
  @Summary
    Reads the value of the GPIO pin, RB0.

  @Description
    Reads the value of the GPIO pin, RB0.

  @Preconditions
    None.
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    </code>

*/
#define IO_RB0_GetValue()         _RB0
/**
  @Summary
    Configures the GPIO pin, RB0, as an input.

  @Description
    Configures the GPIO pin, RB0, as an input.

  @Preconditions
    None.
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#define IO_RB0_SetDigitalInput()  (_TRISB0 = 1)
/**
  @Summary
    Configures the GPIO pin, RB0, as an output.

  @Description
    Configures the GPIO pin, RB0, as an output.

  @Preconditions
    None.
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#define IO_RB0_SetDigitalOutput() (_TRISB0 = 0)
/**
  @Summary
    Sets the GPIO pin, RB1, high using LATB1.

  @Description
    Sets the GPIO pin, RB1, high using LATB1.

  @Preconditions
    The RB1 must be set to an output.
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#define IO_RB1_SetHigh()          (_LATB1 = 1)
/**
  @Summary
    Sets the GPIO pin, RB1, low using LATB1.

  @Description
    Sets the GPIO pin, RB1, low using LATB1.

  @Preconditions
    The RB1 must be set to an output.
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#define IO_RB1_SetLow()           (_LATB1 = 0)
/**
  @Summary
    Toggles the GPIO pin, RB1, using LATB1.

  @Description
    Toggles the GPIO pin, RB1, using LATB1.

  @Preconditions
    The RB1 must be set to an output.
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#define IO_RB1_Toggle()           (_LATB1 ^= 1)
/**
  @Summary
    Reads the value of the GPIO pin, RB1.

  @Description
    Reads the value of the GPIO pin, RB1.

  @Preconditions
    None.
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    </code>

*/
#define IO_RB1_GetValue()         _RB1
/**
  @Summary
    Configures the GPIO pin, RB1, as an input.

  @Description
    Configures the GPIO pin, RB1, as an input.

  @Preconditions
    None.
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#define IO_RB1_SetDigitalInput()  (_TRISB1 = 1)
/**
  @Summary
    Configures the GPIO pin, RB1, as an output.

  @Description
    Configures the GPIO pin, RB1, as an output.

  @Preconditions
    None.
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#define IO_RB15_SetDigitalOutput() (_TRISB15 = 0)
/**
  @Summary
    Sets the GPIO pin, RB2, high using LATB2.

  @Description
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
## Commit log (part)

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2021-03-11 initial software/hardware
2021-03-11 Added screenshot image
2021-03-11 video link
2021-03-11 basic peek/poke to run in stella emulator
2021-03-12 colorize video link
2021-03-12 Louder audio in video example.
2021-03-19 more photos: cart + instruction booklet
2021-03-19 image doc syntax
2021-04-01 Movie output extention changed to '.mvc' Allow for composite test saving using 44100 Hz audio and mov extension.
2021-04-01 Added colorize plugin dll
2021-04-02 testpattern: rotating randomly colored 'MOVIE CART' with pure triangle ramp sound wave.
2021-04-03 Fixed BOM to correct quantities.
2021-04-04 Fixed small ICSP labels on circuit reorganized output folder
2021-04-04 Recompiled pic code to match new to ['M', 'V', 'C', 0 ] field identifier.
2021-04-23 Added more sample movies.
2021-04-25 Encoding interface now includes: Plugin Path, start/end, crop, color, audio options.
2021-04-25 Update Plugin to latest version. Download texture immediately, not next frame. Adding OSX version
2021-04-27 Compiled Colorizer plugin for Mac OSX
2021-05-31 Removed obsolete 'clicky' comment
2021-06-02 Implement kernel format1 for microcontroller
    -Fixes vertical lines artifacts
2021-06-03 Utility to convert from alpha version to format1
2021-06-03 Make video links more apparent with play icon
2021-06-05 Remove partial top + bottom lines to create square
2021-06-11 Keep vblank lines consistently at 36 each field.
2021-08-17 Default crop edge: 20% horizontal, 15% vertical Fixed aspect ratio in preview when using crop.
2021-08-30 Testing colorize options: Clamp values (will likely always On) Background (background color scanline search)
2021-09-03 Latest dll including background selection.
2021-09-07 palette entry typo (caught by Andrew Davie)
2021-09-11 - Make clamping default behaviour
2021-09-11 Update core.asm
    Adapting Thomas Jentzch's kernel modifications to keep left/right sides black.
    Work in progress.
2021-09-12 - Fixed delayed right side kernel
2021-09-13 Refactor memory access to reduce memcpy. Significant performance boost
2021-09-14 - removed unneeded Path + Weight parameters (test case: 235 ms -> 196 ms)
2021-09-14 latest dll compiled
2021-09-14 - compile in vs2019, though earlier versions are still compatible
2021-09-14 add brightness made palette stretching an option move plugin settings to middle
2021-09-14 Revert "- kd-tree causing issues, removed for now"
    This reverts commit 25a3b775cebc3764381812a98d8e142ec17d5512.
2021-09-14 - Embedded timecode font into file, as it may be missing on some systems.
2021-09-14 recompiled dll to latest
2021-09-14 - Saturation slider
2021-09-15 OSX compilation of latest plugin
2021-09-18 - Added 'Preview' slider
2021-09-19 - Preview slider should always land on odd frame to ensure plugin update
2021-09-26 Dont' destroy intermediate files automatically
2021-09-26 includ lst file
2021-10-02 request in float format to avoid cpu conversion
2021-10-02 - Begin with background color search with best result from previous frame (Andrew Davie)
2021-10-02 - small cleanup + recompile
2021-10-02 - faster accumultated error technique (Andrew Davie)
2021-10-02 unused funcs removed
2021-10-02 Add Frame milliseconds to output. Only trail for 2 seconds to get average.
2021-10-03 - precalculate normalized palette, not continuously.
2021-10-03 - small weight optimization (Andrew Davie)
2021-10-03 - 'Bleed During Search' default off. Much quicker (Andrew Davie)
2021-10-03 palette order fixed, new recompile
2021-10-03 -small optimizations from Andrew Davie
2021-10-03 latest compilation
2021-10-03 latest recompilation
2021-10-05 - Improved background search based on hue family (Andrew Davie)
2021-10-06 cleanup common code with lambdas
2021-10-07 masking error on background selection.
2021-10-15 refactoring code to use 2d array class
2021-10-15 - option to search foreground color (unoptimized)
2021-10-15 - more foreground search optimizations
2021-12-29 pic code now up to date with latest encoding and playback changes background color support misc fixes for single stepping and OSD array bounds
2022-01-01 Dialog now includes 'Length' info Length is updated when you press start, not init. Output section labelled 'Encoding'
2023-06-12 Added 'Foreground' color search as option
2023-09-19 NTSL/PAL format. warning before erase reorganized settings better test example
2023-09-23 Updated technical specs for V2
2023-09-24 - saved in earlier build to avoid warning - update range as soon as Movie path change. - F1 message to get back to main dialog - Preview Play option
2023-10-01 Orientation parameter (top/right/bottom/left).
    Uses 2 bits in new format field:
    format 1 ( 1-----TT) TT=Tate (00=top, 01=right, 10=bottom, 11=left)
2023-10-01 tate example
2023-10-11 Refactor to support firmware upgrades
    splitting data+program usage into different sections
    using packed data for title screen
    avoiding debug stack memory
    boot time halved to 0.58msec by delaying all static initialization
    breakup main functions further for re-use
2023-10-14 Allow for 32K or 64K microcontrollers
2023-10-21 colorize: removed junk pixels on last line
2023-10-22 Improved 'Auto Level' for brightening up dark scenes.
2023-10-22 show proper audio output
2023-10-22 Audio: Error diffusion model for better quality at low volume
2023-10-24 Audio: Manual Gain and Error Diffusion adjustments
2023-10-25 Don't lag crop when parked on a frame
2023-10-25 Set plugin path to windows or mac automatically
2023-10-26 Display popup + filename prompt only when file to erase exists.
2023-10-27 bash utility to extract last timecode from mvc file
2023-10-28 Timecode now generated from static images, not font rendering
2023-10-28 better setting defaults.
2023-10-29 long playbar with separate play + record buttons
2023-10-29 audio note
2023-10-29 Turn off Play + Record and end of range
2023-10-30 UI tweaks
    pulse red record indicator
    slower crop/zoom lag
    recenter audio graph
    lock play/pause icons for different systems
2023-10-31 Reset-cancel no longer resets frame position.
2023-11-12 UI reorg
    audio graph smaller, blueish
    zoom now has inner + outer UI, draggable
    zoom lag controllable + vertical zoom fixed.
2023-11-17 timecode is total recorded frames, not current index
2023-11-17 bottom right user selectable favourite settings
2023-11-17 ability to save session
2023-11-19 timeline range fix switching between pal + ntsc
2023-11-19 Resample quality now an option
2023-11-19 'High Quality Resize' giving strange results, disabled.
2023-11-24 Hue-only fastPalette test. ~20% faster.
    Checks colour 0 of each hue, and then all 8 lumninance in
    the best hue. This compares to 2 checks in prior version.
    Results good.
2023-11-25 generalized fastPalette search for foreground/background
    NTSC reverted to previous search
    PAL left at inc=8, but yellowish
2023-11-30 Output on separate page
2023-11-30 record button controls play button
2023-12-10 Controls now recordable in separate pass. Final render option.
2023-12-10 faster python row access when full movie
2023-12-10 reset time when starting final render
2023-12-10 crop parameters were stuck
2023-12-11 Acknowledgements
2023-12-11 MAC OSX recompile to latest
2023-12-12 red/yellow color controls
2023-12-12 red/yellow controls, and disable timeline on finalrender
2023-12-13 atkinson matrix seems lessy noisy
2023-12-14 macosx compile from Andrew Davie
2023-12-16 crop parameters now directly editable again
2023-12-16 broke up controls into more pages (Preview + Output)
2023-12-31 curOffset should be global based on best forecolor floyd-steinberg next pixel weight is 7/16 not 1/16
2023-12-31 bleed control uniform
2023-12-31 different test setup
2024-01-01 uniform weights for floydsteinberg, atkinson
2024-01-02 testing background overrides, and smaller background searchers
2024-01-03 timecode can be encoded directly, no need for dithering plugin
2024-01-04 Useful 1..500 number output with constant sine
2024-01-05 FramesInit redundant, save 2 bytes
2024-01-07 multiple cpu-shader pass test
2024-01-07 comparison
2024-01-11 initial 3 lines
2024-01-13 simple make+launch script
2024-01-14 optimizing multi-pass
2024-01-15 speed change comments
2024-01-16 testing multiple frames
2024-01-17 vsync off to not clamp at monitor rate
2024-01-19 implementing gpu/cpu encoder
2024-01-19 gpu/cpu choice
2024-01-20 quality control for gpu render
2024-01-20 more dialog re-org
2024-01-20 fixed missing top line, better centering on lower quality
2024-01-21 removed extra page division
2024-01-21 quality now controls color search again, not vertical resolution
2024-01-21 fixed signed/unsigned comparison causing hang past/before file ends
2024-01-21 switching bool to bits to save memory
2024-01-21 updated firmware binaries
2024-01-24 Preview Delay slider
2024-01-27 overlay timeline with yellow bands were control settings are recorded
2024-01-30 release notes cleanup
2024-02-18 PCB: reduce the post radius closer to original: 3.175 -> 3.190
    Most boards still accepted the 1/4" post.
2024-02-24 Pre-Order information
2024-02-24 formatting
2024-02-25 test commit
2024-03-05 gerber files
2024-03-08 just the title screen, and how it was rebuilt from firmware
2024-03-10 Exposed basic kernel as small bin file with expected output.
2024-03-12 better use of macros
2024-03-12 default to ntsc for kernel demo
2024-03-14 more thank yous
2024-03-24 Test patch to select on A12 vs A11, allows 7800 usage (but not FB2)
2024-04-06 PAL, 7800 support
    Must select on A12(and)A11, not just A11, as A11 used by 7800.
    Kernel revised to avoid improper HMOVE that behaves badly on some TIA
    variants (Kool Aid Man fix), especially on PAL Jr's
2024-04-07 Title screeen supports PAL, etc.
    Takes on height of first field it reads.
2024-04-13 content updating notes
2024-04-15 PAL60 content
2024-04-21 avoid the title screen glitch when sampling the first frame for format PAL will still show NTSC for a few seconds before switching over
2024-05-06 todo about hole sizes
2024-05-15 board 2.32: hole size increased from 3.19 to 3.373
2024-05-16 gerber files and rerouting away from post hole slightly
2024-05-17 When 'Automatic Gain Control' used, option to limit max audio gain.
2024-05-20 SECAM should be 50Hz not 60Hz
2024-06-01 lowered audio error diffusion setting from 1.0 to 0.25 for less hiss
2024-06-30 injection molded shell notes firmware update notes
2024-09-02 each function isolated in separate section to make future patching easier exposing more defines for patch use patch standin
2024-09-03 max line size too small when labels encountered
2024-09-11 patch1 : multifile support. cycle through files on the moviecart with 'SELECT' button.
2024-09-14 Patch to give early rc1 test unit, multi-select patch
2024-10-15 new section to allow ._CNCInterrupt to change in size
2024-10-26 separate bootloader + kernel fixes
    separate bootloader section that contains FLASH
    and other utilities independent of regular main code
    No longer relies on exact memory locations.
    Wipe out full section and rewrite.
    Avoid writes to ROM
    PAL 7800: output consistent value for 7E00-7EFF to pass startup check
2024-10-29 color_char bins for device testing
2024-10-29 more consistent naming
2024-12-01 moved old hex files to legacy folder for clarity
2024-12-23 More specific firmware updating instructions.
2025-05-10 Sikor style PCB
2025-10-19 Reset switch -> rewind 10 seconds Select switch -> switch to next movie as before When movie ends, automatically start next movie.
2025-10-20 Full kernel patch to now play all mvc files sequentially on the SD card. This patch replaces the entire firmware, is permanent and can brick the card if not installed correctly. Use with caution.
2025-10-21 fixed repeat error codes bumped internal eeprom version to 0202
2025-11-27 V2.3 left and right joystick work interchangeably start in timecode/shuttle mode
2025-12-11 elf and map files for previous releases
2025-12-26 patch fixes to not erase inside executing code. patch upgraded to 2.3

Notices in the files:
firmware/bootloader/mcc_generated_files/pin_manager.h:
(c) 2020 Microchip Technology Inc. and its subsidiaries. You may use this
pic/mcc_generated_files/pin_manager.h:
(c) 2018 Microchip Technology Inc. and its subsidiaries.
parts and their libraries:
parts_mc2: COPYRIGHT: Copyright (C) 2022 Ultra Librarian. All rights reserved.
COPYRIGHT: Copyright (C) 2025 Ultra Librarian. All rights reserved.
